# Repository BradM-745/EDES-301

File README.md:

<h1>EDES-301</h1>
<p>Repository for EDES-301 course work</p>

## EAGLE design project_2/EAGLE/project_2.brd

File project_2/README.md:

<h1>Etch-a-Sketch PCB:</h1>
<p>This project used a PocketBeagle and an SPI screen to create a simple digital Etch-a-Sketch project!</p>

<h2>Features:</h2>
<p> This project utilizes an SPI screen to enable the use of colors when drawing. Two potentiometers\n
are used to draw on the screen. To change colors, a button on the back of the board can be pressed to cycle
between red, green, and blue. The device can be turned on or off by pressing the power button on the \n
back of the board. The project can easily be expanded by using the included USB port.</p>
<h2>Documentation:</h2>
<p>To build the PCB, refer to the docs folder in this repository. The schematics show how to wire and assemble the board. Manufacturer information can be found under the MFG folder.</p>

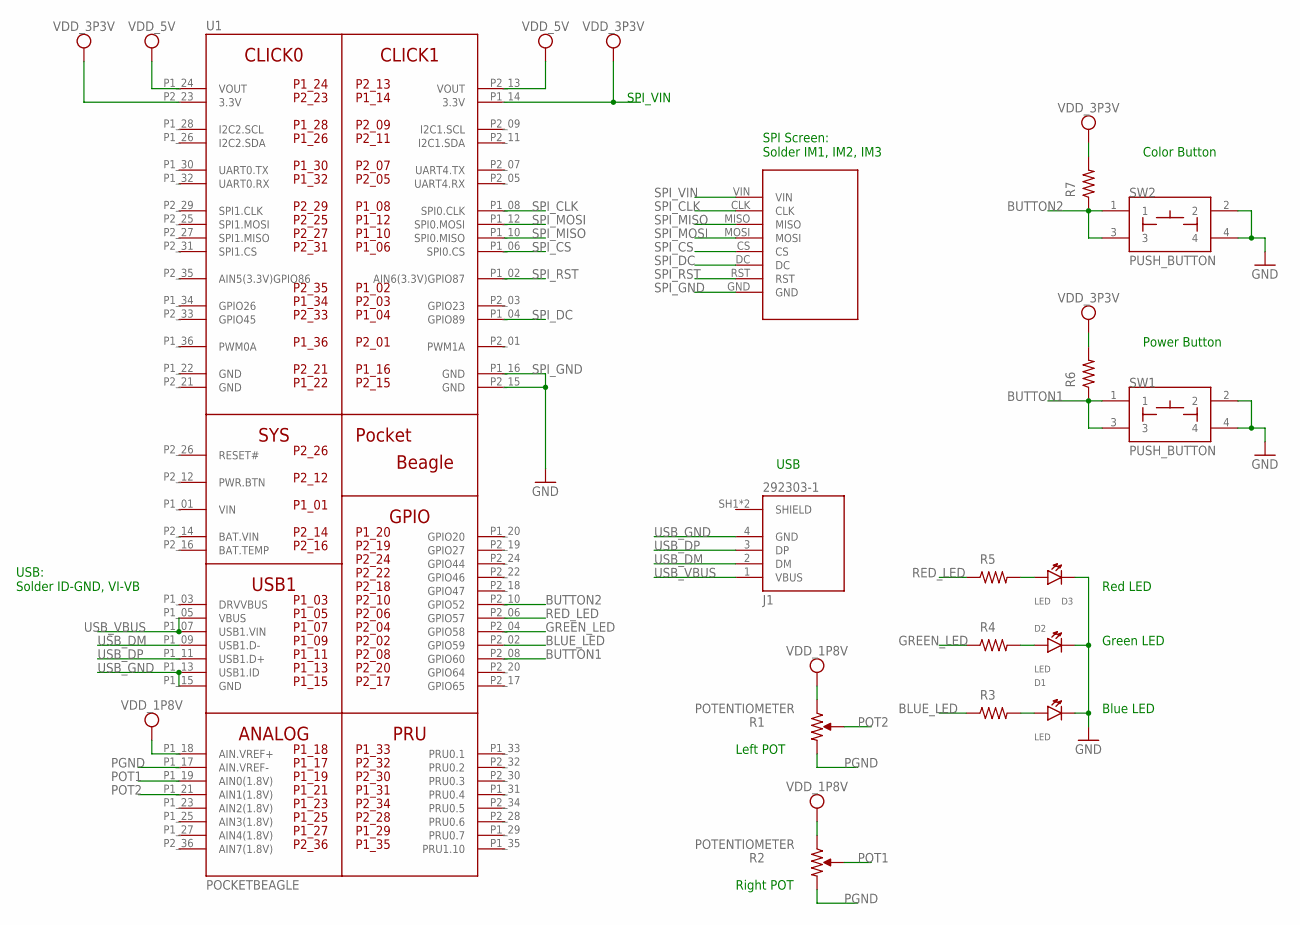
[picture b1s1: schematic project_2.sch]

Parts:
D1, D2, D3: LED; EIA-STD
J1: 292303-1; TE_292303-1
R1, R2: POTENTIOMETER; POT-PO90S
R3, R4, R5, R6, R7: R_R0805; R0805
SW1, SW2: PUSH_BUTTON; BUTTON_12.5MM
U1: POCKETBEAGLE
U$1: SCREEN

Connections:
BAT.VIN: U1.P2_14 (BAT.VIN)
BLUE_LED: R3.1, U1.P2_02 (GPIO59)
BUTTON1: R6.1, SW1.1, SW1.3, U1.P2_08 (GPIO60)
BUTTON2: R7.1, SW2.1, SW2.3, U1.P2_10 (GPIO52)
GND: D1.CATHODE, D2.CATHODE, D3.CATHODE, SW1.2, SW1.4, SW2.2, SW2.4, U1.P1_22 (GND), U1.P2_21 (GND)
GREEN_LED: R4.1, U1.P2_04 (GPIO58)
unnamed: D3.ANODE, R5.2
unnamed: D2.ANODE, R4.2
unnamed: D1.ANODE, R3.2
PGND: R1.CW, R2.CW, U1.P1_17 (AIN.VREF-)
POT1: R2.S, U1.P1_19 (AIN0(1.8V))
POT2: R1.S, U1.P1_21 (AIN1(1.8V))
RED_LED: R5.1, U1.P2_06 (GPIO57)
SPI_CLK: U1.P1_08 (SPI0.CLK), U$1.CLK
SPI_CS: U1.P1_06 (SPI0.CS), U$1.CS
SPI_DC: U1.P1_04 (GPIO89), U$1.DC
SPI_GND: U1.P1_16 (GND), U1.P2_15 (GND), U$1.GND
SPI_MISO: U1.P1_10 (SPI0.MISO), U$1.MISO
SPI_MOSI: U1.P1_12 (SPI0.MOSI), U$1.MOSI
SPI_RST: U1.P1_02 (AIN6(3.3V)GPIO87), U$1.RST
SPI_VIN: U$1.VIN
USB_DM: J1.2 (DM), U1.P1_09 (USB1.D-)
USB_DP: J1.3 (DP), U1.P1_11 (USB1.D+)
USB_GND: J1.4 (GND), U1.P1_13 (USB1.ID), U1.P1_15 (GND)
USB_VBUS: J1.1 (VBUS), U1.P1_05 (VBUS), U1.P1_07 (USB1.VIN)
VDD_1P8V: R1.CCW, R2.CCW, U1.P1_18 (AIN.VREF+)
VDD_3P3V: R6.2, R7.2, U1.P1_14 (3.3V), U1.P2_23 (3.3V)
VDD_5V: U1.P1_24 (VOUT), U1.P2_13 (VOUT)
VIN: U1.P1_01 (VIN)

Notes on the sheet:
USB: Solder ID-GND, VI-VB
SPI Screen: Solder IM1, IM2, IM3
SPI_VIN
USB
Red LED
Green LED
Blue LED
Left POT
Right POT
Power Button
Color Button

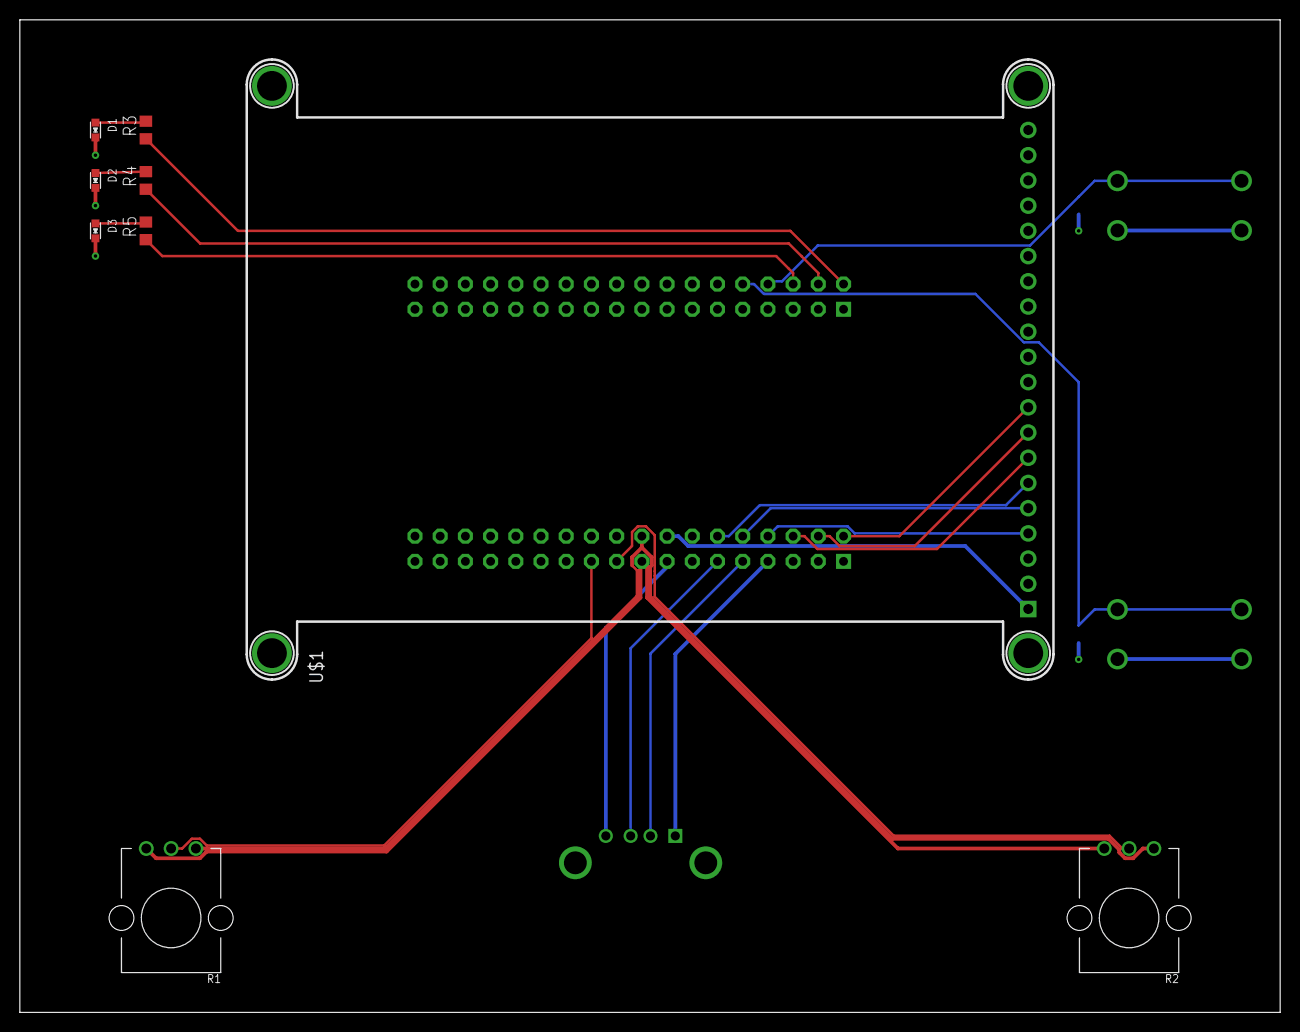
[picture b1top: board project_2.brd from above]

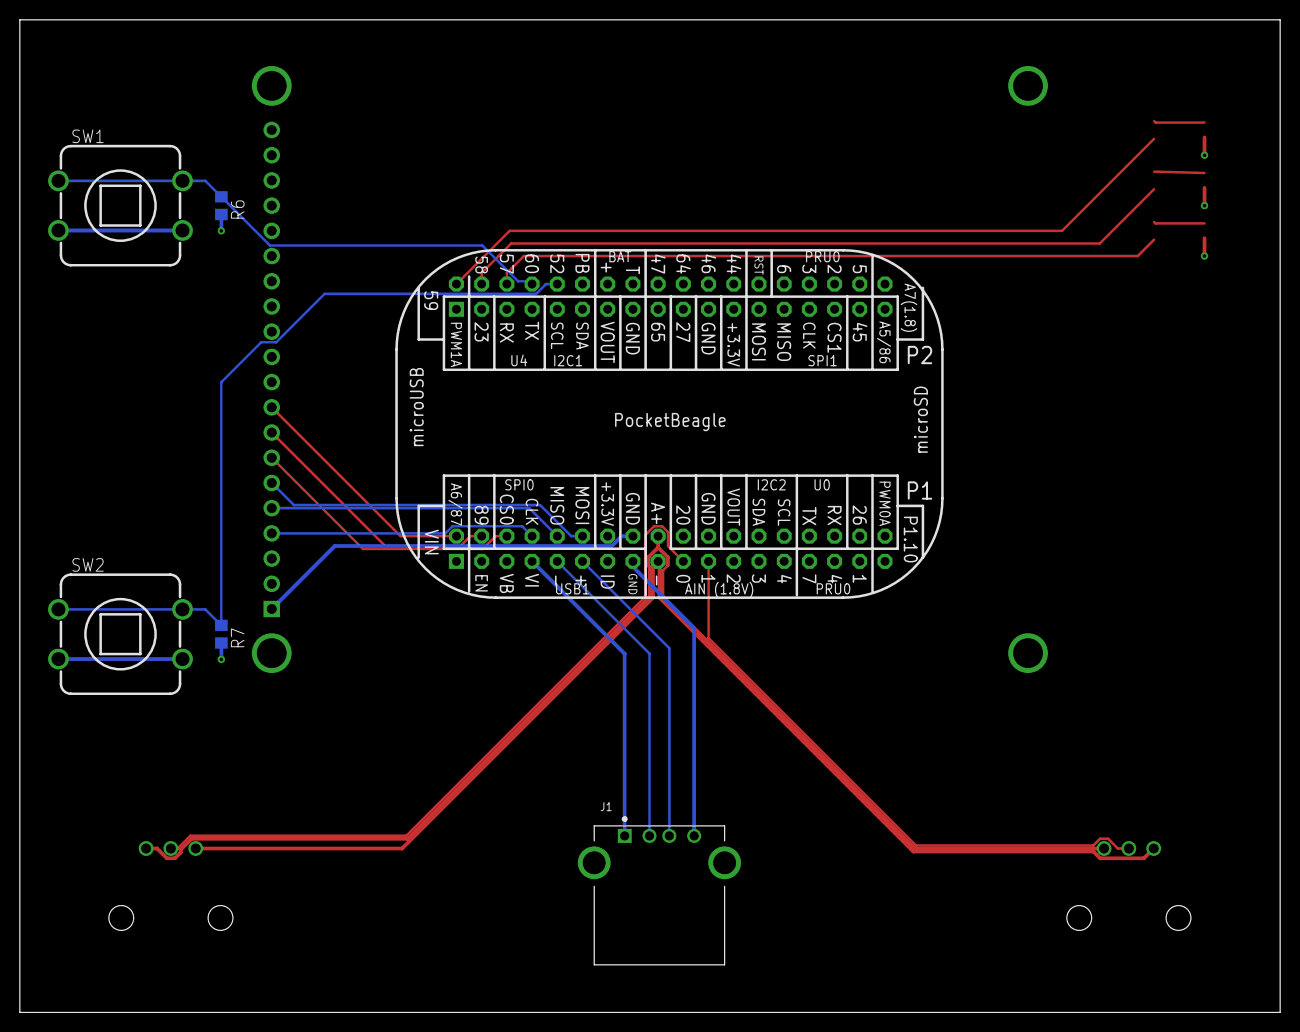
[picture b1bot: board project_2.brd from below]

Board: 4 copper layers, 127.0 x 100.0 mm, 15 parts (6 on the bottom side), 26 nets.

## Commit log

2024-10-01 Create project_01
    contains all my work on project one
